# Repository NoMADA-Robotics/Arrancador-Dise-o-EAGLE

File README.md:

# Arrancador-Dise-o-EAGLE
Diseño en Hardware de Arrancador para Robótica de Competición en EAGLE

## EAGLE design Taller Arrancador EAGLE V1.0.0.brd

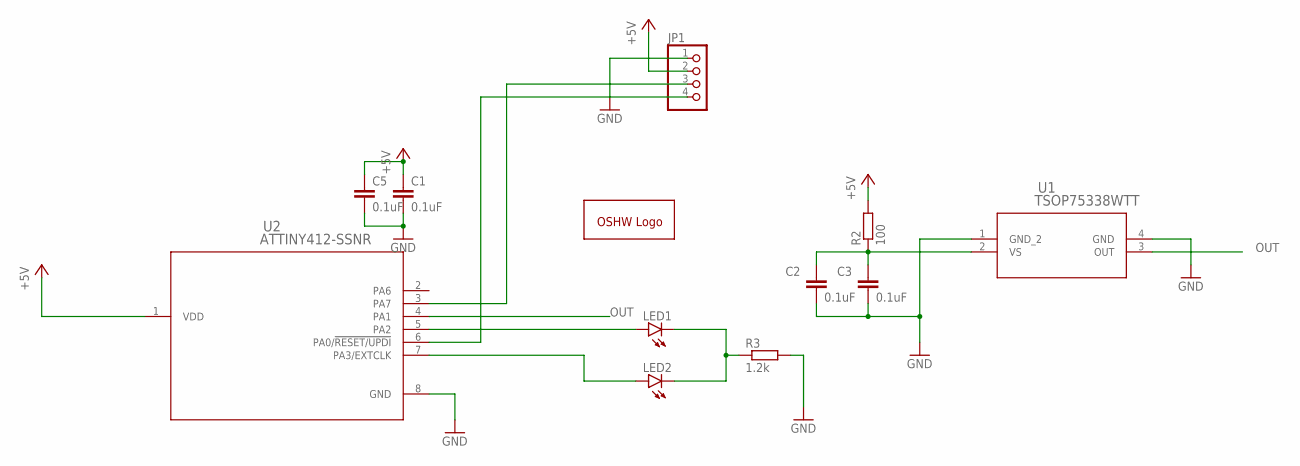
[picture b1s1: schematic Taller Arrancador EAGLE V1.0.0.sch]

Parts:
C1, C5: 0.1uF; C0603
C2, C3: 0.1uF; C0402
GOLD_ORB_SM1: OSHWLOGOLOGO5MM; OSHW_5MM
JP1: PINHD-1X04_2.54-S; 1X04-S
LED1, LED2: LEDCHIP-LED0603; CHIP-LED0603
R2: 100; R0603
R3: 1.2k; R0603
U1: TSOP75338WTT; TSOP75338WTT_VIS
U2: ATTINY412-SSNR; SOIC8_SA_SST_MCH

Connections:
+5V: C1.1, C5.1, JP1.2, R2.2, U2.1 (VDD)
GND: C1.2, C2.2, C3.2, C5.2, JP1.1, R3.2, U1.1 (GND_2), U1.4 (GND), U2.8 (GND)
unnamed: C2.1, C3.1, R2.1, U1.2 (VS)
unnamed: LED1.A, U2.5 (PA2)
unnamed: LED2.A, U2.7 (PA3/EXTCLK)
unnamed: LED1.C, LED2.C, R3.1
OUT: U1.3 (OUT), U2.4 (PA1)
SEÑAL: JP1.3, U2.3 (PA7)
UPDI: JP1.4, U2.6 (PA0/!RESET/UPDI)

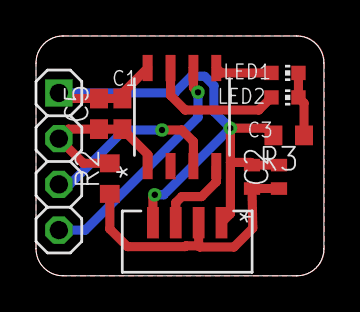
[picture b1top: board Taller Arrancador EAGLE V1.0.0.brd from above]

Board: 2 copper layers, 16.0 x 13.3 mm, 12 parts (1 on the bottom side), 9 nets.

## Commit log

2021-03-12 .
    .

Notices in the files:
parts and their libraries:
COPYRIGHT: Copyright (C) 2018 Accelerated Designs. All rights reserved
